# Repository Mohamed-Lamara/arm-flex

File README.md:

# ARM Flex
Github Repository for a Training Assistant Embedded System Project.

*Work in Progress*

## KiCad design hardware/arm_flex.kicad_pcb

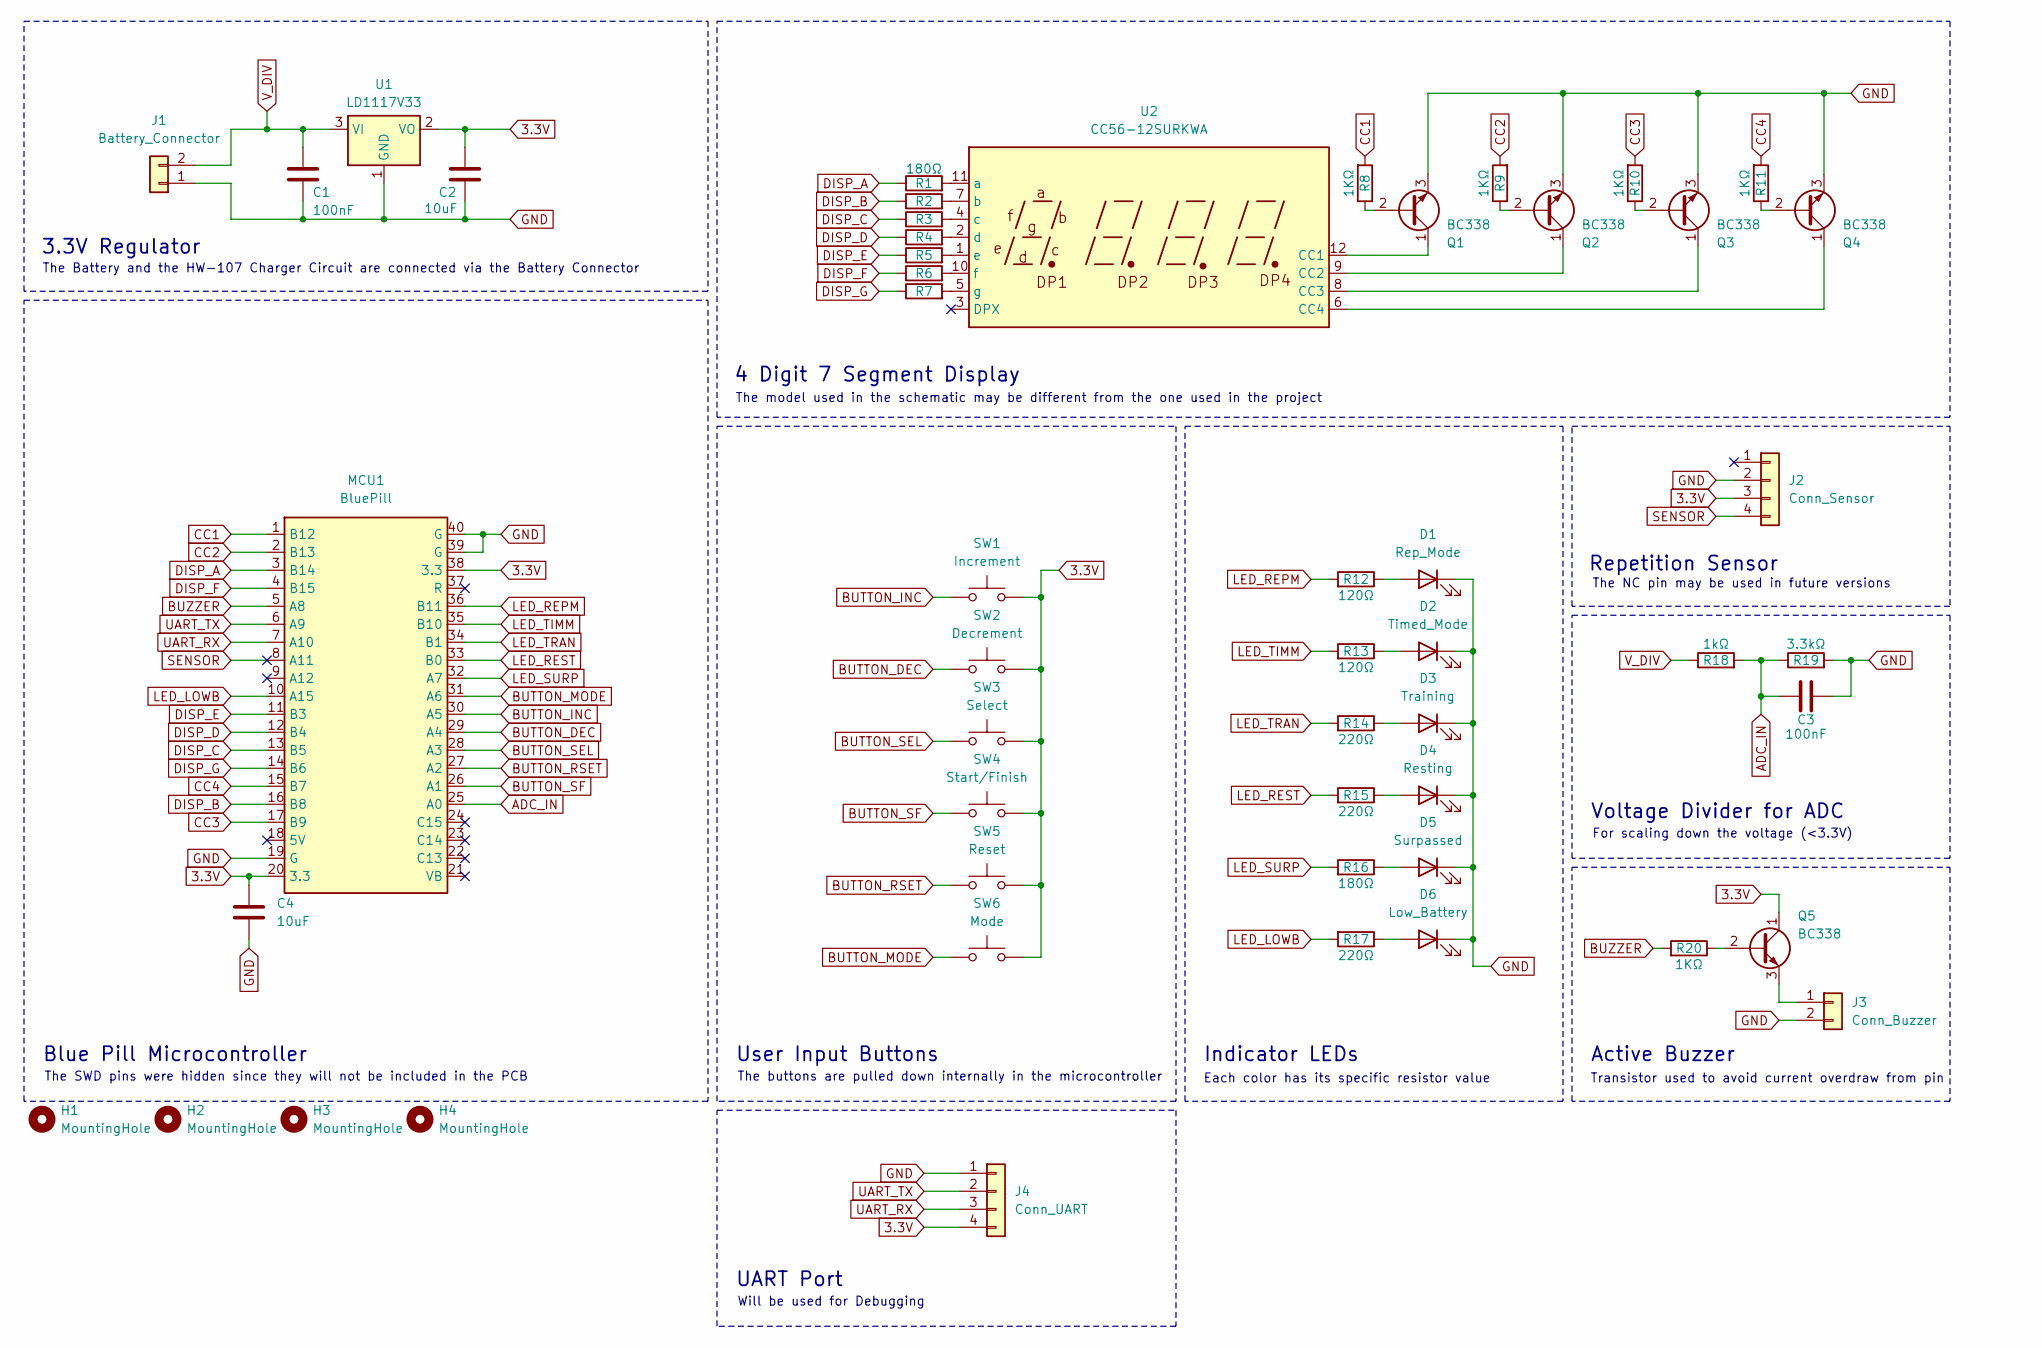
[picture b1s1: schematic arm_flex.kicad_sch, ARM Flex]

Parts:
C1, C3: 100nF; C_Disc_D3.0mm_W2.0mm_P2.50mm
C2, C4: 10uF; C_Disc_D3.0mm_W2.0mm_P2.50mm
D1: Rep_Mode; LED_D3.0mm
D2: Timed_Mode; LED_D3.0mm
D3: Training; LED_D3.0mm
D4: Resting; LED_D3.0mm
D5: Surpassed; LED_D3.0mm
D6: Low_Battery; LED_D3.0mm
H1, H2, H3, H4: MountingHole; MountingHole_2.2mm_M2_DIN965_Pad
J1: Battery_Connector; JST_EH_B2B-EH-A_1x02_P2.50mm_Vertical
J2: Conn_Sensor; JST_EH_B4B-EH-A_1x04_P2.50mm_Vertical
J3: Conn_Buzzer; PinHeader_1x02_P1.00mm_Vertical
J4: Conn_UART; JST_EH_B4B-EH-A_1x04_P2.50mm_Vertical
MCU1: BluePill
Q1, Q2, Q3, Q4, Q5: BC338; TO-92_Inline
R1, R2, R3, R4, R5, R6, R7: 180Ω; R_Axial_DIN0204_L3.6mm_D1.6mm_P5.08mm_Horizontal
R8, R9, R10, R11: 1KΩ; R_Axial_DIN0204_L3.6mm_D1.6mm_P5.08mm_Horizontal
R12, R13: 120Ω; R_Axial_DIN0204_L3.6mm_D1.6mm_P1.90mm_Vertical
R14, R15, R17: 220Ω; R_Axial_DIN0204_L3.6mm_D1.6mm_P1.90mm_Vertical
R16: 180Ω; R_Axial_DIN0204_L3.6mm_D1.6mm_P1.90mm_Vertical
R18: 1kΩ; R_Axial_DIN0204_L3.6mm_D1.6mm_P5.08mm_Horizontal
R19: 3.3kΩ; R_Axial_DIN0204_L3.6mm_D1.6mm_P5.08mm_Horizontal
R20: 1KΩ; R_Axial_DIN0204_L3.6mm_D1.6mm_P1.90mm_Vertical
SW1: Increment; SW_PUSH-12mm_Wuerth-430476085716
SW2: Decrement; SW_PUSH-12mm_Wuerth-430476085716
SW3: Select; SW_PUSH-12mm_Wuerth-430476085716
SW4: Start/Finish; SW_PUSH-12mm_Wuerth-430476085716
SW5: Reset; SW_PUSH-12mm_Wuerth-430476085716
SW6: Mode; SW_PUSH-12mm_Wuerth-430476085716
U1: LD1117V33; TO-220-3_Horizontal_TabUp
U2: CC56-12SURKWA; CA56-12SURKWA

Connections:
3.3V: C2.1, C4.1, J2.3, J4.4, MCU1.20 (3.3), MCU1.38 (3.3), Q5.1 (C), SW1.2, SW2.2, SW3.2, SW4.2, SW5.2, SW6.2, U1.2 (VO); also elsewhere on the board
ADC_IN: C3.1, MCU1.25 (A0), R18.2, R19.1
BUTTON_DEC: MCU1.29 (A4), SW2.1
BUTTON_INC: MCU1.30 (A5), SW1.1
BUTTON_MODE: MCU1.31 (A6), SW6.1
BUTTON_RSET: MCU1.27 (A2), SW5.1
BUTTON_SEL: MCU1.28 (A3), SW3.1
BUTTON_SF: MCU1.26 (A1), SW4.1
BUZZER: MCU1.5 (A8), R20.2
CC1: MCU1.1 (B12), R8.2
CC2: MCU1.2 (B13), R9.2
CC3: MCU1.17 (B9), R10.2
CC4: MCU1.15 (B7), R11.2
DISP_A: MCU1.3 (B14), R1.1
DISP_B: MCU1.16 (B8), R2.1
DISP_C: MCU1.13 (B5), R3.1
DISP_D: MCU1.12 (B4), R4.1
DISP_E: MCU1.11 (B3), R5.1
DISP_F: MCU1.4 (B15), R6.1
DISP_G: MCU1.14 (B6), R7.1
GND: C1.2, C2.2, C3.2, C4.2, D1.1 (K), D2.1 (K), D3.1 (K), D4.1 (K), D5.1 (K), D6.1 (K), J1.1, J2.2, J3.2, J4.1, MCU1.19 (G), MCU1.39 (G), MCU1.40 (G), Q1.3 (E), Q2.3 (E), Q3.3 (E), Q4.3 (E), R19.2, U1.1 (GND); also elsewhere on the board
LED_LOWB: MCU1.10 (A15), R17.2
LED_REPM: MCU1.36 (B11), R12.2
LED_REST: MCU1.33 (B0), R15.2
LED_SURP: MCU1.32 (A7), R16.2
LED_TIMM: MCU1.35 (B10), R13.2
LED_TRAN: MCU1.34 (B1), R14.2
unnamed: D1.2 (A), R12.1
unnamed: D2.2 (A), R13.1
unnamed: D3.2 (A), R14.1
unnamed: D4.2 (A), R15.1
unnamed: D5.2 (A), R16.1
unnamed: D6.2 (A), R17.1
unnamed: J3.1, Q5.3 (E)
unnamed: Q1.2 (B), R8.1
unnamed: Q1.1 (C), U2.12 (CC1)
unnamed: Q2.2 (B), R9.1
unnamed: Q2.1 (C), U2.9 (CC2)
unnamed: Q3.2 (B), R10.1
unnamed: Q3.1 (C), U2.8 (CC3)
unnamed: Q4.2 (B), R11.1
unnamed: Q4.1 (C), U2.6 (CC4)
unnamed: Q5.2 (B), R20.1
unnamed: R1.2, U2.11 (a)
unnamed: R2.2, U2.7 (b)
unnamed: R3.2, U2.4 (c)
unnamed: R4.2, U2.2 (d)
unnamed: R5.2, U2.1 (e)
unnamed: R6.2, U2.10 (f)
unnamed: R7.2, U2.5 (g)
SENSOR: J2.4, MCU1.8 (A11)
UART_RX: J4.3, MCU1.7 (A10); also elsewhere on the board
UART_TX: J4.2, MCU1.6 (A9); also elsewhere on the board
V_DIV: C1.1, J1.2, R18.1, U1.3 (VI)

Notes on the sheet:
The Battery and the HW-107 Charger Circuit are connected via the Battery Connector
UART Port
Active Buzzer
The NC pin may be used in future versions
Indicator LEDs
The buttons are pulled down internally in the microcontroller
Repetition Sensor
Voltage Divider for ADC
4 Digit 7 Segment Display
Will be used for Debugging
Each color has its specific resistor value
The model used in the schematic may be different from the one used in the project
For scaling down the voltage (<3.3V)
3.3V Regulator
The SWD pins were hidden since they will not be included in the PCB
User Input Buttons
Transistor used to avoid current overdraw from pin
Blue Pill Microcontroller

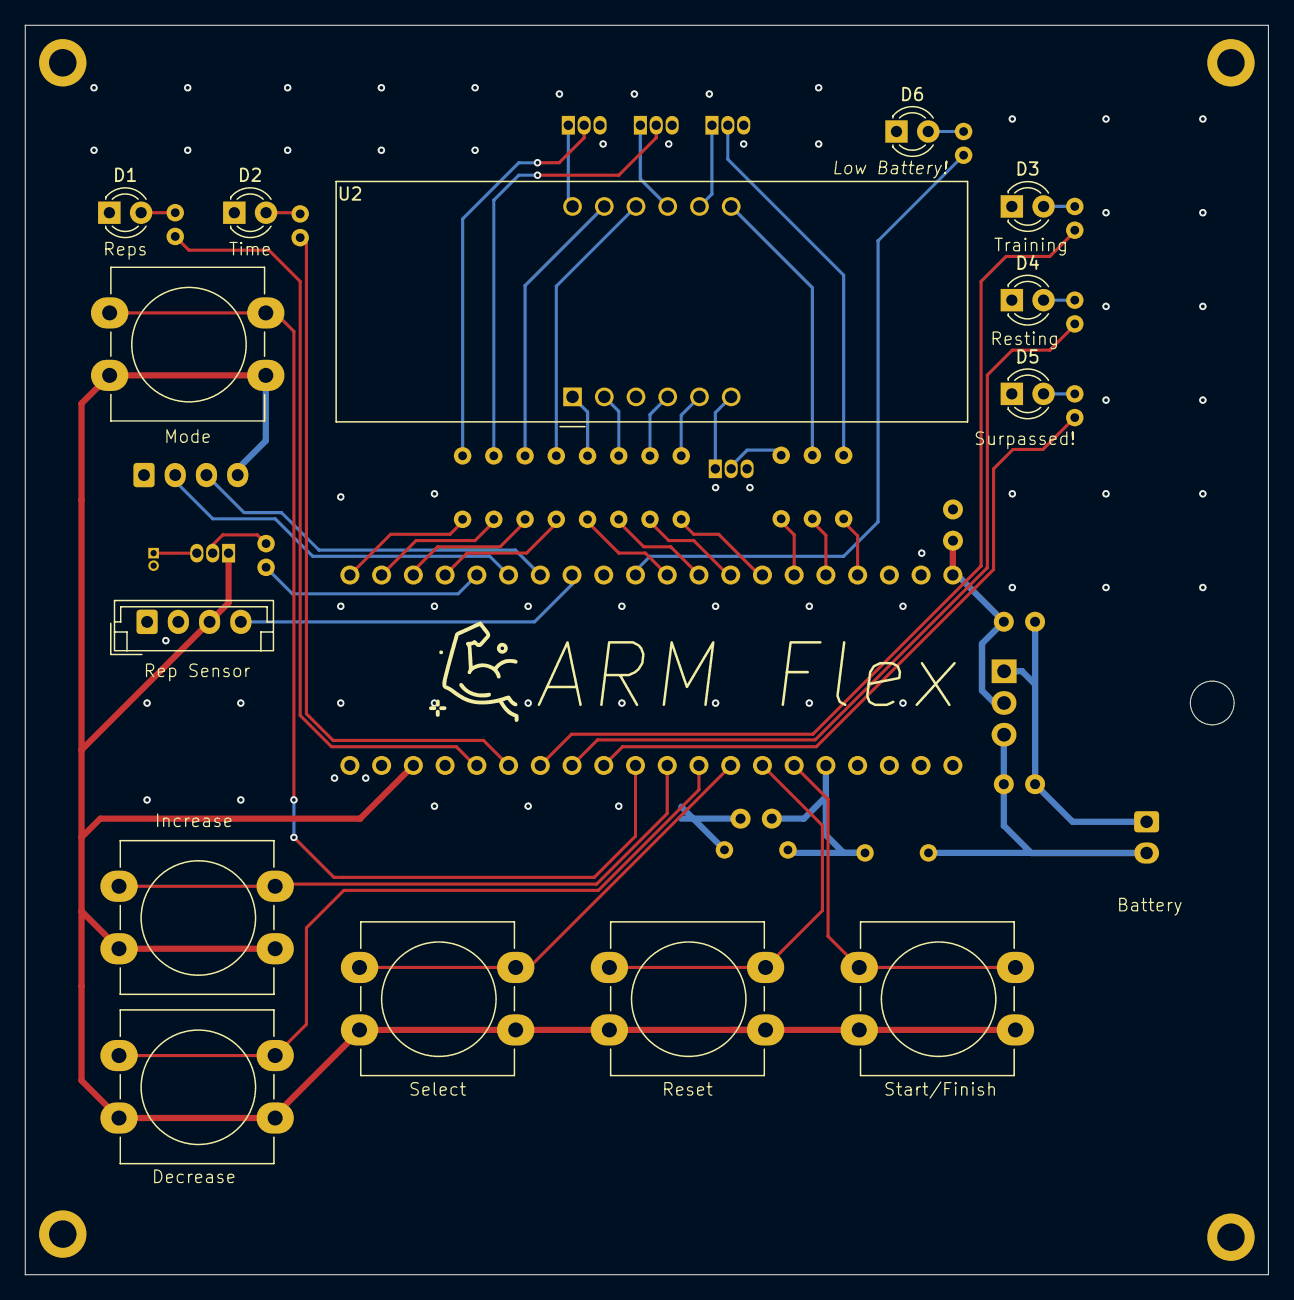
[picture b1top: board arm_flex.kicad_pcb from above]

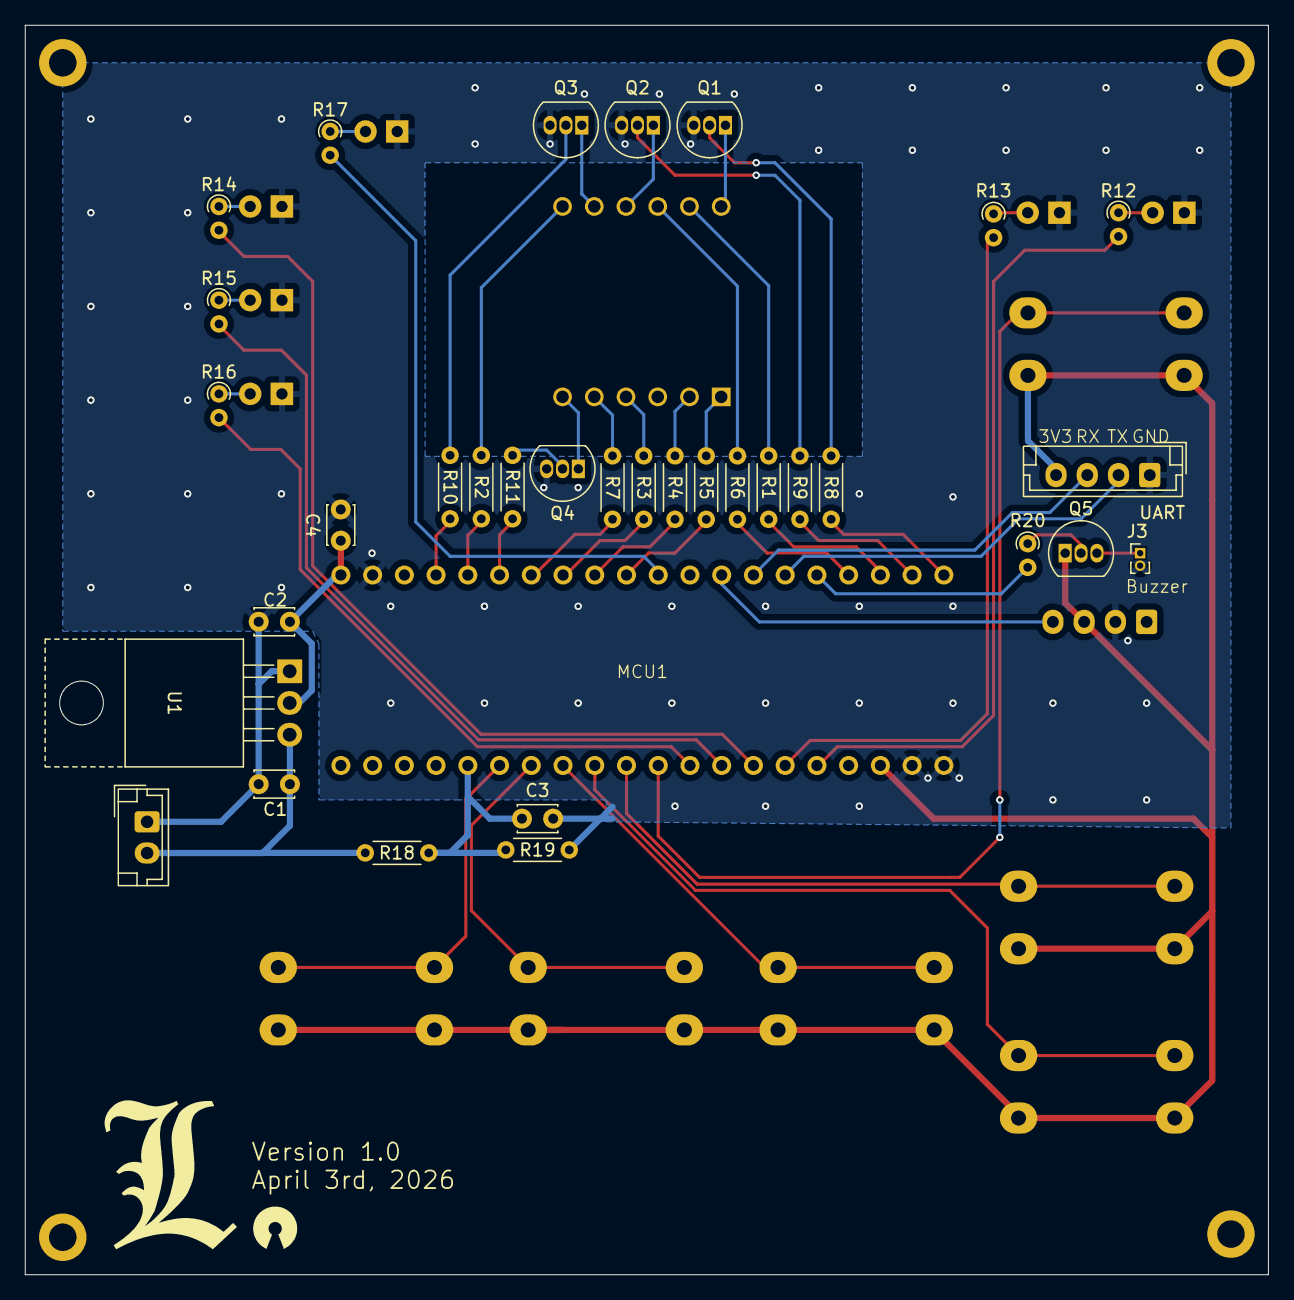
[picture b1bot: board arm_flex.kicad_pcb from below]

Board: 2 copper layers, 99.5 x 100.0 mm, 52 parts (34 on the bottom side), 54 nets.

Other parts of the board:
UART: Conn_UART; JST_EH_B4B-EH-A_1x04_P2.50mm_Vertical

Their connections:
3.3V: UART.4; also elsewhere on the board
GND: UART.1; also elsewhere on the board
UART_RX: UART.3; also elsewhere on the board
UART_TX: UART.2; also elsewhere on the board

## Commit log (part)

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2026-02-03 Add temporary placeholder
2026-02-07 Rename Block Diagram.png to block-diagram.png
2026-02-07 Rename Software Architecture.png to software-architecture.png
2026-02-07 Rename State Machine.png to state-machine.png
2026-02-07 Fix Project Design Document.md
2026-02-13 Update README.md
    Rename the Project's name
2026-02-13 Update Project Design Document.md
    - Changed Project Name
    - Modified Hardware Decisions Section
